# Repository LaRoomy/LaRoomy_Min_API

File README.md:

# LaRoomy_Min_API

## Description
This is a minimized Version of the LaRoomy Api written in C and is optimized for 8 bit microcontroller. It's not platform specific: It can be used in conjunction with all controllers which have an externally bluetooth hardware or bluetooth capabilities included.

To get an introduction, a description of the concept behind and further info to the LaRoomy API vistit the [website](https://api.laroomy.com/p/get-started.html#genInfoHd)

## Implementation
> [!NOTE]
> This is a short outline of the implementation terminology.
> 
>  To get detailed info [click here](https://api.laroomy.com/2023/07/minimized-api-version-for-8bit-systems.html) to visit the respective page on the LaRoomy Api Website.

**To implement the LaRoomy functionality in your project the following steps are necessary:**

### Definitions
- Define unique identifier for all properties which should be added to the api, this makes it easy to work with the properties later.
- Create global device property struct parameter as data-holder for the LaRoomy Api. Please note that this api is written for controller with very limited system resources, that means even though the properties are added to the api, the api does not execute dynamic memory allocation, the api only saves references to the preliminary defined parameters and put them on stack which is managed by the api.
- If device properties with complex state type are used, the respective complex property state struct must be also created as data-holder
- Define a callback function for all events that should be processed in your project.

### Setup
- Initialize all device-property structs
- Fill the device-property structs with the property data
- Add the properties to the api
- Add the complex property state data-holder to the api (if applicable)
- Register the callback(s) to receive remote events
- Register the gateway function for outgoing data

### Loop
- Check for incoming data periodically and forward it to the api if there was data to process

### Important

Since the minimized LaRoomy Api is a generalized implementation of the transmission handling to interact with the LaRoomy App, the api does not automatically receive or send data.
To implement the API in the existing logic, the data to sent and the data which is received must be bypassed to the api by registering a gateway function for each direction, respectively.

To enable the api to send data a function must be decared which handles the send operation for Bluetooth data and a reference to the function must be passed to the LaRoomy Api:
``` C
// define a function which handles data output
// (in this case a bluetooth module with transparent uart is used)
void sendBLEData(const char* data)
{
    if(data != NULL)
    {
        USART_WriteString(data);
    }
}

// set the usart output gateway for the laroomy api
// - the internal transmission control will use this function to send data
setOutGateway(sendBLEData);
```
If data is received through the bluetooth line, it must be passed to the 'onDataReceived' function of the LaRoomy Api to process it:
``` C
// when data is received from the gateway, this function must be called to process the data
// - this is critical for the api to work correctly
void onDataReceived(const char *data);
```

## Examples
Included in this repository are [examples](https://github.com/LaRoomy/LaRoomy_Min_API/tree/main/Examples) created with the Microchip Studio IDE. They use a combination of an Atmega328P and a Microchip RN4871 Bluetooth Module.

The underlying schematic and board data is created with the Eagle Layout Editor and included in this repository. [Show it](https://github.com/LaRoomy/LaRoomy_Min_API/tree/main/Test_Circuit)

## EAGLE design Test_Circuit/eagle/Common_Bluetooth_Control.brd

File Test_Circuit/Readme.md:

# Common Bluetooth Control Board
The aim of this construction was to create an own development board for the Microchip RN4871. Why doing this? Because all other available boards with bluetooth capabilities are consuming too much current. I wanted something that is tailor made for the LaRoomy Api and has a minimum power consumption.
If the RN4871 is configured in the right way and the power-down sleep mode of the atmega328 is used, the power consumption of the board is lower than 100µA and remains a fully functional and connectable bluetooth device.

This schematic/board is used in all examples in this repository.

If the shutdown mode of the RN4871 is used, the 1Hz square wave interrupt of the Microchip MCP79410 is used to generate a sucessive wakeup condition so that the bluetooth module is only used a short period of a time interval to advertise and may receive a connection and the input voltage regulator is not used (for example by powering through a micro cell battery), the current consumption can be reduced to an average value of 5µA.

With the MAX16910 input voltage regulator, the input voltage can range from 4.2V to 30V.

## Board

## Schematic

Logic Section:

3.3V Power Generation:

## Final assembly

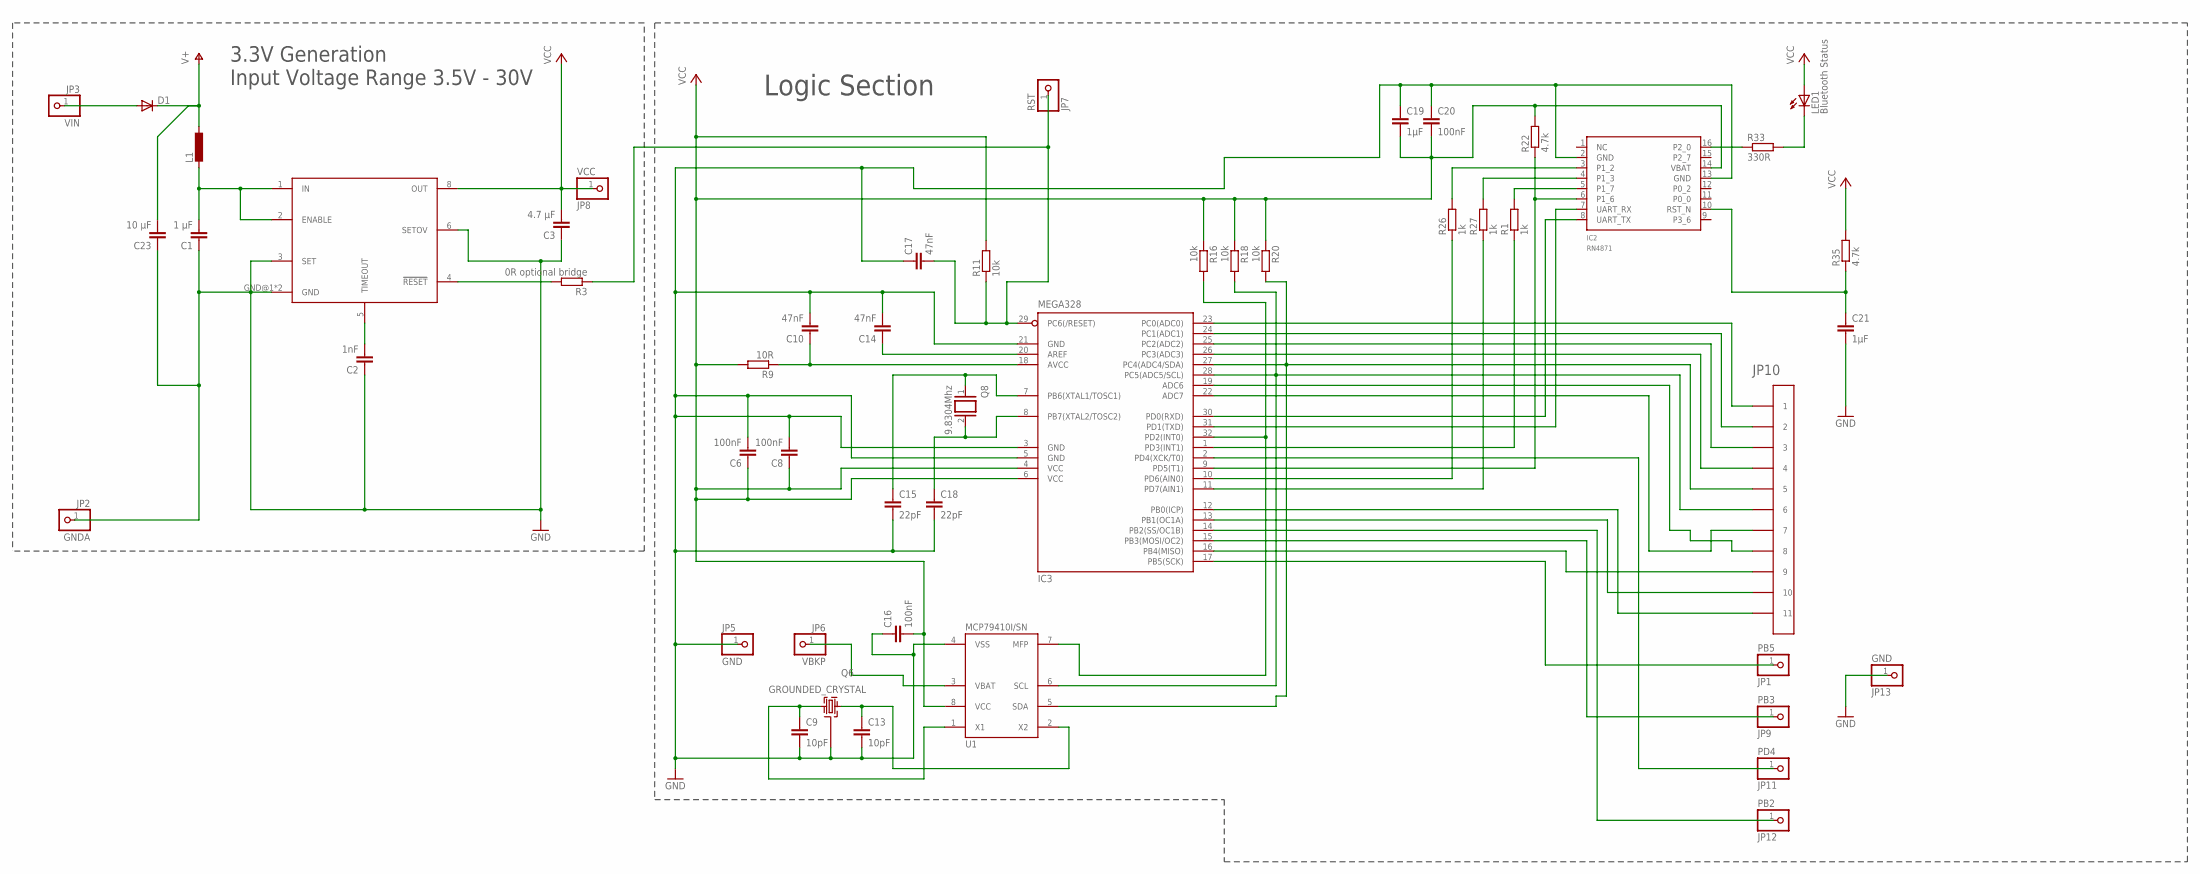
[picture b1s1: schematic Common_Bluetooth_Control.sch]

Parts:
C1: 1 µF; C1206
C2: 1nF; C0603
C3: 4.7 µF; C1206
C6, C16, C20: 100nF; C0603
C8: 100nF; C0603K
C9, C13: 10pF; C0603
C10, C14, C17: 47nF; C0603
C15, C18: 22pF; C0805
C19, C21: 1µF; C0603
C23: 10 µF; C1206
D1: DIODE-DO214AC; DO214AC
IC1: MAX16910; SO08
IC2: RN4871
IC3: MEGA328; TQFP32-08
JP1: PB5; 1X01
JP2: GNDA; 1X01
JP3: VIN; 1X01
JP5, JP13: GND; 1X01
JP6: VBKP; 1X01
JP7: RST; 1X01
JP8: VCC; 1X01
JP9: PB3; 1X01
JP10: PINHD-1X11-OCT; 1X11_OCT
JP11: PD4; 1X01
JP12: PB2; 1X01
L1: L-EUL0805; R0805
LED1: Bluetooth Status; CHIPLED_0603
Q6: GROUNDED_CRYSTAL; MS3V-7
Q8: 9.8304Mhz; QS
R1, R26, R27: 1k; R0603
R3: 0R optional bridge; R0603
R9: 10R; R0603
R11, R16, R18, R20: 10k; R0603
R22, R35: 4.7k; R0603
R33: 330R; R0603
U1: MCP79410I/SN; SO8

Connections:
GND: C1.1, C2.1, C3.1, C6.2, C8.2, C9.2, C10.2, C13.2, C14.2, C15.2, C16.1, C17.1, C18.2, C19.1, C20.1, C21.2, C23.1, IC1.3 (SET), IC1.6 (SETOV), IC1.GND@1 (GND), IC1.GND@2 (GND), IC2.2 (GND), IC2.13 (GND), IC3.3 (GND), IC3.5 (GND), IC3.21 (GND), JP2.1, JP5.1, JP13.1, Q6.GND, U1.4 (VSS)
unnamed: C13.1, Q6.X2 (2), U1.2 (X2)
unnamed: C21.1, IC2.10 (RST_N), R35.1
unnamed: IC2.16 (P2_0), R33.1
unnamed: IC3.32 (PD2(INT0)), R16.2, U1.7 (MFP)
unnamed: C9.1, Q6.X1 (1), U1.1 (X1)
unnamed: IC2.3 (P1_2), R26.2
unnamed: LED1.C, R33.2
unnamed: IC2.8 (UART_TX), IC3.30 (PD0(RXD))
unnamed: IC2.7 (UART_RX), IC3.31 (PD1(TXD))
unnamed: D1.A, JP3.1
unnamed: C10.1, IC3.18 (AVCC), R9.1
unnamed: IC3.16 (PB4(MISO)), JP10.9
unnamed: C14.1, IC3.20 (AREF)
unnamed: C15.1, IC3.7 (PB6(XTAL1/TOSC1)), Q8.1
unnamed: JP6.1, U1.3 (VBAT)
unnamed: C18.1, IC3.8 (PB7(XTAL2/TOSC2)), Q8.2
unnamed: IC2.4 (P1_3), R27.2
unnamed: IC3.17 (PB5(SCK)), JP1.1
unnamed: IC3.11 (PD7(AIN1)), R27.1
unnamed: IC3.10 (PD6(AIN0)), R26.1
unnamed: IC2.6 (P1_6), IC3.9 (PD5(T1)), R22.1
unnamed: IC3.28 (PC5(ADC5/SCL)), JP10.1 (6), R18.2, U1.6 (SCL)
unnamed: IC3.27 (PC4(ADC4/SDA)), JP10.2 (5), R20.2, U1.5 (SDA)
unnamed: IC2.5 (P1_7), R1.2
unnamed: IC3.1 (PD3(INT1)), R1.1
unnamed: IC3.23 (PC0(ADC0)), JP10.5 (1)
unnamed: IC3.24 (PC1(ADC1)), JP10.6 (2)
unnamed: IC3.25 (PC2(ADC2)), JP10.4 (3)
unnamed: IC3.26 (PC3(ADC3)), JP10.3 (4)
unnamed: IC3.19 (ADC6), JP10.8
unnamed: IC3.22 (ADC7), JP10.7
unnamed: IC3.2 (PD4(XCK/T0)), JP11.1
unnamed: IC3.12 (PB0(ICP)), JP10.11
unnamed: IC3.13 (PB1(OC1A)), JP10.10
unnamed: IC3.14 (PB2(SS/OC1B)), JP12.1
unnamed: C2.2, IC1.5 (TIMEOUT)
unnamed: IC1.4 (!RESET!), R3.2
unnamed: C1.2, IC1.1 (IN), IC1.2 (ENABLE), L1.2
unnamed: IC3.15 (PB3(MOSI/OC2)), JP9.1
unnamed: C17.2, IC3.29 (PC6(/RESET)), JP7.1, R3.1, R11.1
V+: C23.2, D1.C, L1.1
VCC: C3.2, C6.1, C8.1, C16.2, C19.2, C20.2, IC1.8 (OUT), IC2.14 (VBAT), IC3.4 (VCC), IC3.6 (VCC), JP8.1, LED1.A, R9.2, R11.2, R16.1, R18.1, R20.1, R22.2, R35.2, U1.8 (VCC)

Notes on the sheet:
Logic Section
3.3V Generation Input Voltage Range 3.5V - 30V

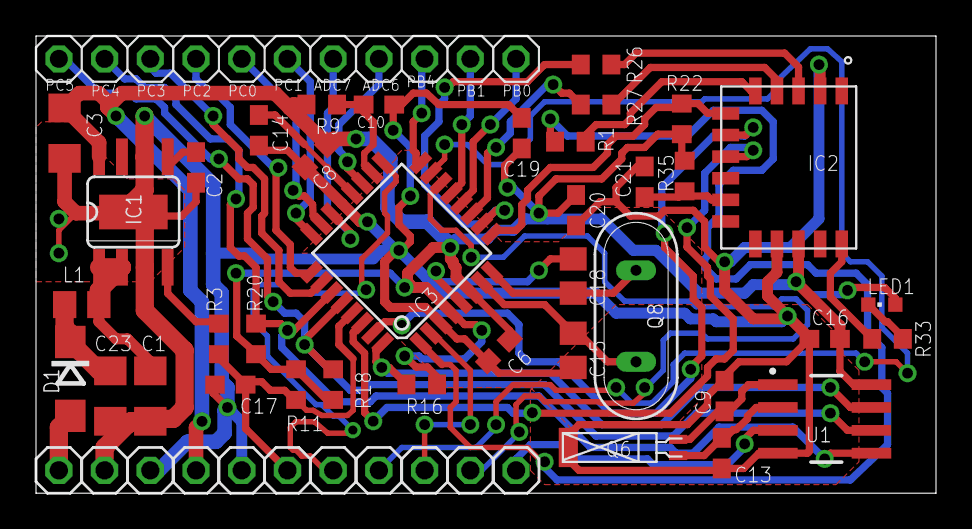
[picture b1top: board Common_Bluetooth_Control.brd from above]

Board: 2 copper layers, 50.0 x 25.4 mm, 50 parts (0 on the bottom side), 43 nets.

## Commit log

2023-07-04 Board and schematic images added
2023-07-13 Update H13-07-2023-1
2023-07-14 Examples added
